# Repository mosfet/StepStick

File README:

http://reprap.org/wiki/StepStick

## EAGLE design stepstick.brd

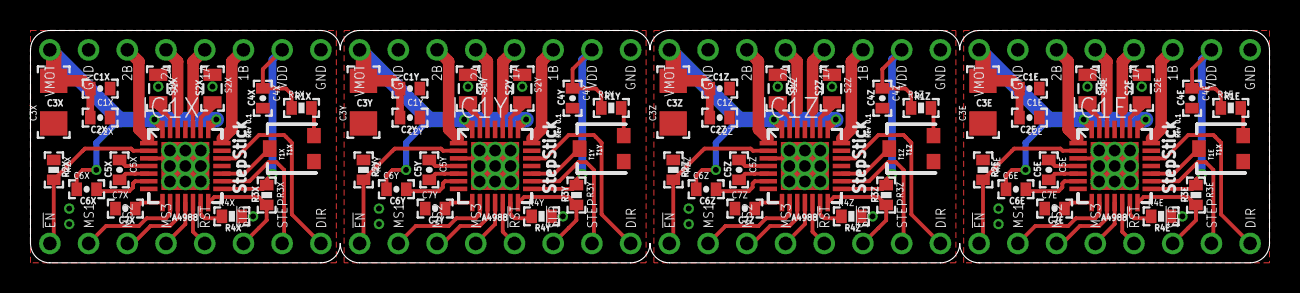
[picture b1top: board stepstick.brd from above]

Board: 2 copper layers, 81.3 x 15.2 mm, 64 parts (0 on the bottom side), 87 nets.

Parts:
C1E, C1X, C1Y, C1Z, C2E, C2X, C2Y, C2Z, C5E, C5X, C5Y, C5Z, C6E, C6X, C6Y, C6Z: .1uf; 0402-CAP
C3E, C3X, C3Y, C3Z: 4.7uF; 1206
C4E, C4X, C4Y, C4Z, C7E, C7X, C7Y, C7Z: .22uf; 0402-CAP
IC1E, IC1X, IC1Y, IC1Z: A4988; QFN28ET
J1E, J1X, J1Y, J1Z: CLONOLU
R1E, R1X, R1Y, R1Z: 20k; 0402-RES
R2E, R2X, R2Y, R2Z, R3E, R3X, R3Y, R3Z: 100k; 0402-RES
R4E, R4X, R4Y, R4Z: 10k; 0402-RES
S1E, S1X, S1Y, S1Z, S2E, S2X, S2Y, S2Z: 0.2; 0805
T1E, T1X, T1Y, T1Z: TRIM; TRIMPOT-3MM

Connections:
ECP1: C5E.1, IC1E.4
ECP2: C5E.2, IC1E.5
EDIR: IC1E.19, J1E.DIR
EENABLE: IC1E.2, J1E.!EN, R2E.2
EMS1: IC1E.9, J1E.MS1
EMS2: IC1E.10, J1E.MS2
EMS3: IC1E.11, J1E.MS3
EOUT1A: IC1E.24, J1E.1A
EOUT1B: IC1E.21, J1E.1B
EOUT2A: IC1E.26, J1E.2A
EOUT2B: IC1E.1, J1E.2B
EREF: IC1E.17, T1E.2
EREF2: R1E.2, T1E.3
ERESET: IC1E.12, J1E.!RST
EROSC: IC1E.13, R4E.1
ESENSE1: IC1E.23, S2E.2
ESENSE2: IC1E.27, S1E.2
ESLEEP: IC1E.14, J1E.!SLP, R3E.2
ESTEP: IC1E.16, J1E.STEP
EVCP: C6E.2, IC1E.6
EVREG: C7E.2, IC1E.8
GND: C1E.1, C1X.1, C1Y.1, C1Z.1, C2E.1, C2X.1, C2Y.1, C2Z.1, C3E.1, C3X.1, C3Y.1, C3Z.1, C4E.2, C4X.2, C4Y.2, C4Z.2, C7E.1, C7X.1, C7Y.1, C7Z.1, IC1E.3, IC1E.7, IC1E.18, IC1E.20, IC1E.25, IC1E.EXP, IC1X.3, IC1X.7, IC1X.18, IC1X.20, IC1X.25, IC1X.EXP, IC1Y.3, IC1Y.7, IC1Y.18, IC1Y.20, IC1Y.25, IC1Y.EXP, IC1Z.3, IC1Z.7, IC1Z.18, IC1Z.20, IC1Z.25, IC1Z.EXP, J1E.GND$1, J1E.GND$2, J1X.GND$1, J1X.GND$2, J1Y.GND$1, J1Y.GND$2, J1Z.GND$1, J1Z.GND$2, R2E.1, R2X.1, R2Y.1, R2Z.1, R4E.2, R4X.2, R4Y.2, R4Z.2, S1E.1, S1X.1, S1Y.1, S1Z.1, S2E.1, S2X.1, S2Y.1, S2Z.1, T1E.1, T1X.1, T1Y.1, T1Z.1
VDD: C4E.1, C4X.1, C4Y.1, C4Z.1, IC1E.15, IC1X.15, IC1Y.15, IC1Z.15, J1E.VDD, J1X.VDD, J1Y.VDD, J1Z.VDD, R1E.1, R1X.1, R1Y.1, R1Z.1, R3E.1, R3X.1, R3Y.1, R3Z.1
VMOT: C1E.2, C1X.2, C1Y.2, C1Z.2, C2E.2, C2X.2, C2Y.2, C2Z.2, C3E.2, C3X.2, C3Y.2, C3Z.2, C6E.1, C6X.1, C6Y.1, C6Z.1, IC1E.22, IC1E.28, IC1X.22, IC1X.28, IC1Y.22, IC1Y.28, IC1Z.22, IC1Z.28, J1E.VMOT, J1X.VMOT, J1Y.VMOT, J1Z.VMOT
XCP1: C5X.1, IC1X.4
XCP2: C5X.2, IC1X.5
XDIR: IC1X.19, J1X.DIR
XENABLE: IC1X.2, J1X.!EN, R2X.2
XMS1: IC1X.9, J1X.MS1
XMS2: IC1X.10, J1X.MS2
XMS3: IC1X.11, J1X.MS3
XOUT1A: IC1X.24, J1X.1A
XOUT1B: IC1X.21, J1X.1B
XOUT2A: IC1X.26, J1X.2A
XOUT2B: IC1X.1, J1X.2B
XOUT2B1: IC1Y.1, J1Y.2B
XREF: IC1X.17, T1X.2
XREF2: R1X.2, T1X.3
XRESET: IC1X.12, J1X.!RST
XROSC: IC1X.13, R4X.1
XSENSE1: IC1X.23, S2X.2
XSENSE2: IC1X.27, S1X.2
XSLEEP: IC1X.14, J1X.!SLP, R3X.2
XSTEP: IC1X.16, J1X.STEP
XVCP: C6X.2, IC1X.6
XVREG: C7X.2, IC1X.8
YCP1: C5Y.1, IC1Y.4
YCP2: C5Y.2, IC1Y.5
YDIR1: IC1Y.19, J1Y.DIR
YENABLE: IC1Y.2, J1Y.!EN, R2Y.2
YMS1: IC1Y.9, J1Y.MS1
YMS2: IC1Y.10, J1Y.MS2
YMS3: IC1Y.11, J1Y.MS3
YOUT1A: IC1Y.24, J1Y.1A
YOUT1B: IC1Y.21, J1Y.1B
YOUT2A: IC1Y.26, J1Y.2A
YREF: IC1Y.17, T1Y.2
YREF1: R1Y.2, T1Y.3
YRESET: IC1Y.12, J1Y.!RST
YROSC: IC1Y.13, R4Y.1
YSENSE1: IC1Y.23, S2Y.2
YSENSE2: IC1Y.27, S1Y.2
YSLEEP: IC1Y.14, J1Y.!SLP, R3Y.2
YSTEP: IC1Y.16, J1Y.STEP
YVCP: C6Y.2, IC1Y.6
YVREG: C7Y.2, IC1Y.8
ZCP1: C5Z.1, IC1Z.4
ZCP2: C5Z.2, IC1Z.5
ZDIR: IC1Z.19, J1Z.DIR
ZENABLE: IC1Z.2, J1Z.!EN, R2Z.2
ZMS1: IC1Z.9, J1Z.MS1
ZMS2: IC1Z.10, J1Z.MS2
ZMS3: IC1Z.11, J1Z.MS3
ZOUT1A: IC1Z.24, J1Z.1A
ZOUT1B: IC1Z.21, J1Z.1B
ZOUT2A: IC1Z.26, J1Z.2A
ZOUT2B: IC1Z.1, J1Z.2B
ZREF: IC1Z.17, T1Z.2
ZREF2: R1Z.2, T1Z.3
ZRESET: IC1Z.12, J1Z.!RST
ZROSC: IC1Z.13, R4Z.1
ZSENSE1: IC1Z.23, S2Z.2
ZSENSE2: IC1Z.27, S1Z.2
ZSLEEP: IC1Z.14, J1Z.!SLP, R3Z.2
ZSTEP: IC1Z.16, J1Z.STEP
ZVCP: C6Z.2, IC1Z.6
ZVREG: C7Z.2, IC1Z.8

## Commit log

2011-03-19 Initial Checkin
2011-03-23 added readme
2011-04-22 updated to latest version, created parts.txt
2011-04-22 added gerbers
2013-11-27 enabled soldering of A4988 by heating the bottom.
    By having the square of the bottom side of the PCB bare, you apply a
    generous amount of flux, and placing the chip on the top, and heating
    and applying solder to the bottom, will then flow the chip on.
